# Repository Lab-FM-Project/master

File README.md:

# master
FMProject master folder

Second year FM project. Based on the AR1010 FM chip. We got to play around with it and add any innovations. (Even if its only 10% of the mark!)

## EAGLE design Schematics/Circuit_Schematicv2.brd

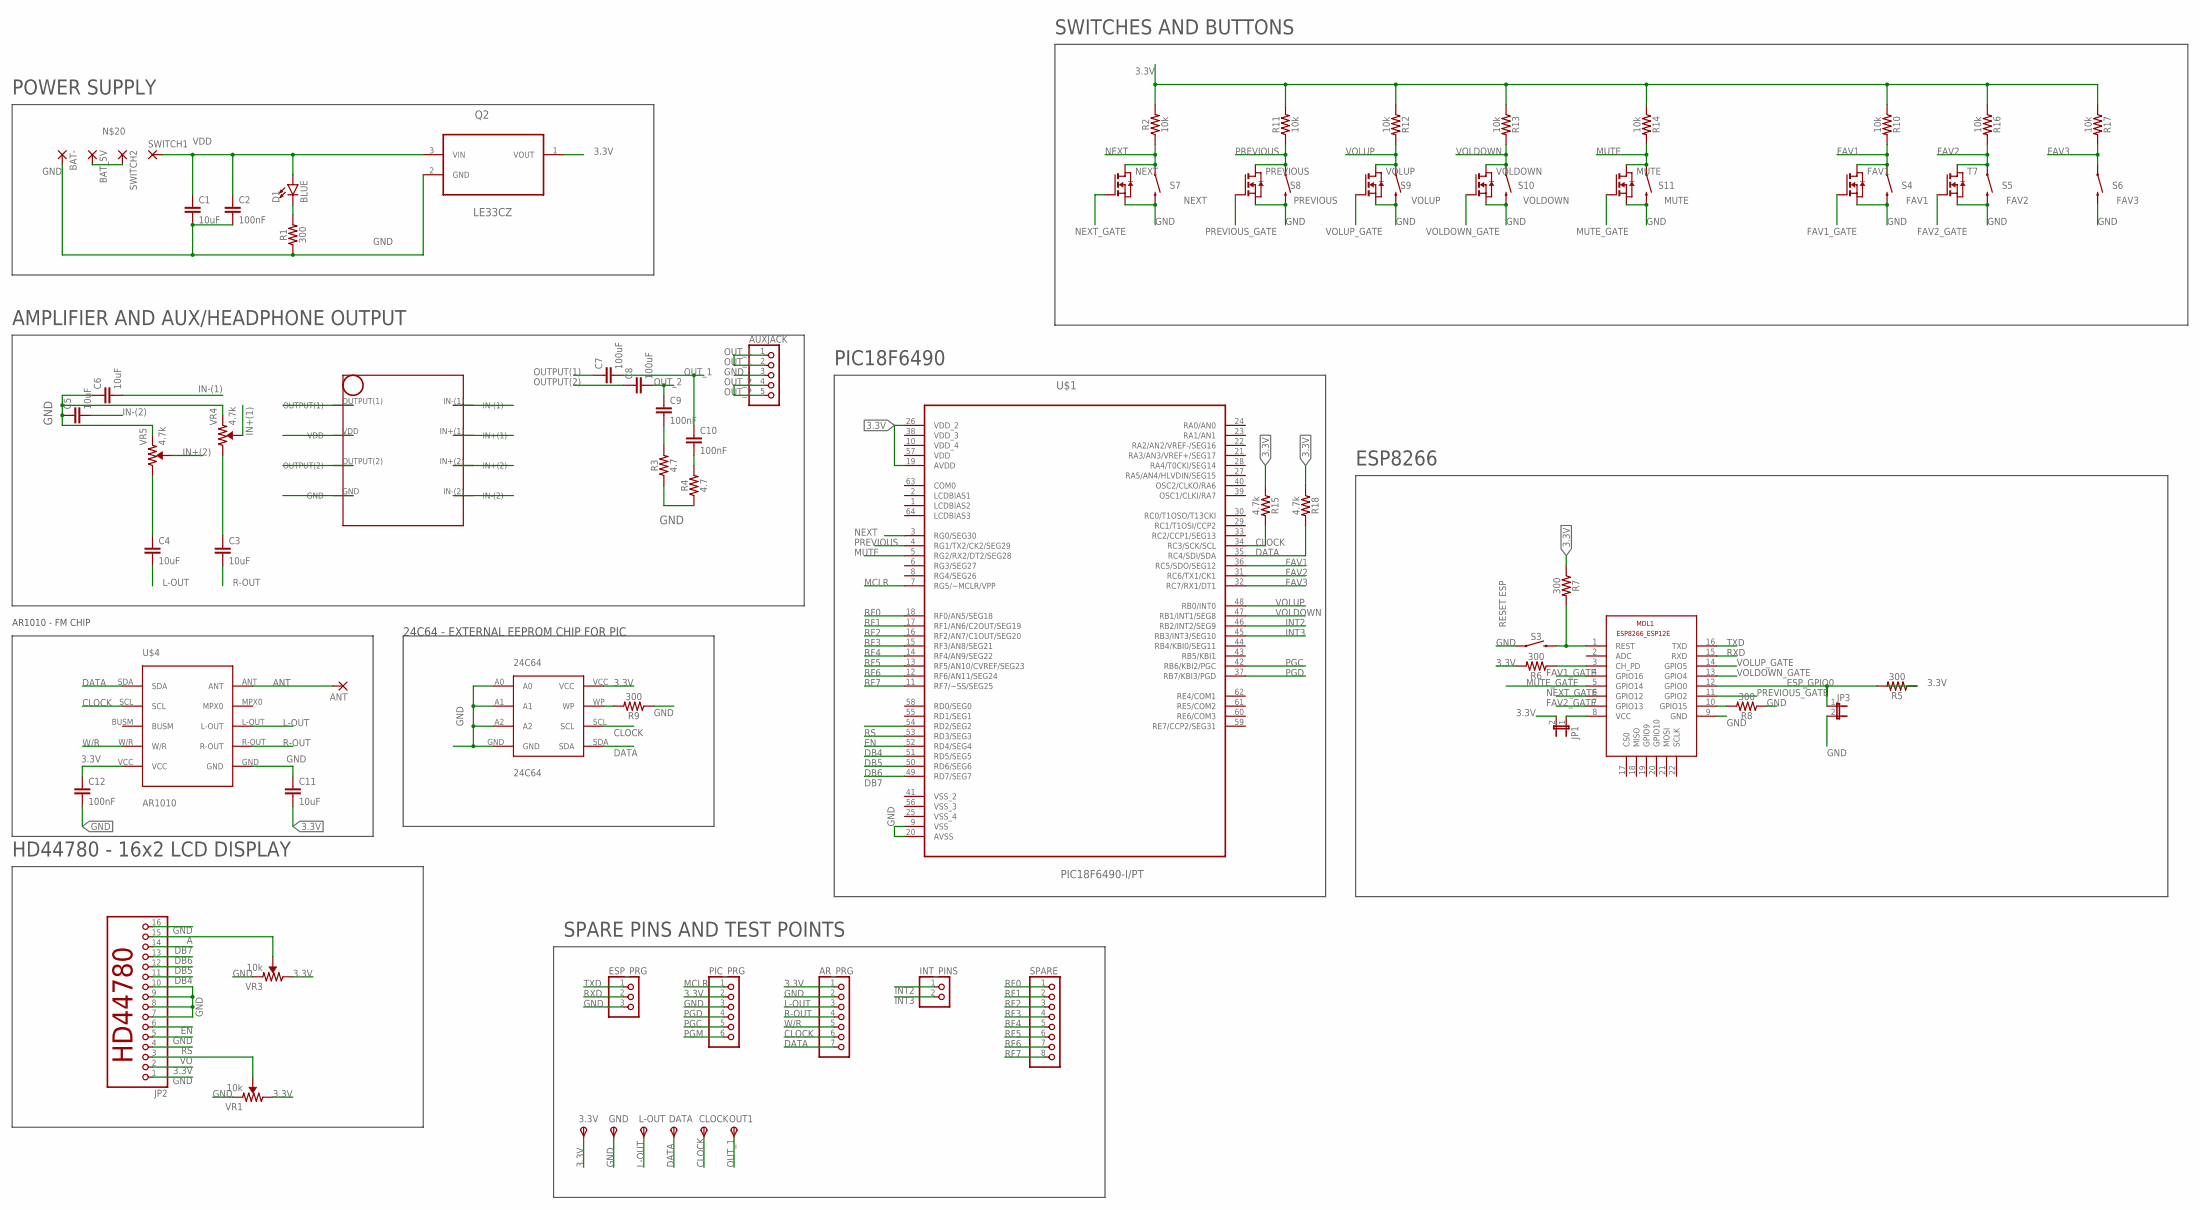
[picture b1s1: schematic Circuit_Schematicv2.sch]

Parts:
3.3V: TPSPAD1-13; P1-13
24C64: 24C64; SOIC-8
ANT: 2,15/1,0
AR_PRG: PINHD-1X7; 1X07
AUXJACK: PINHD-1X5; 1X05
BAT-: 2,15/1,0
BAT_5V: 2,15/1,0
C1, C3, C4, C5, C6, C11: 10uF; 1210
C2, C9, C10, C12: 100nF; 1210
C7, C8: 100uF; 1210
CLOCK: TPSPAD1-13; P1-13
D1: BLUE; LED-1206
DATA: TPSPAD1-13; P1-13
ESP_PRG: PINHD-1X3; 1X03
FAV1: NMOSSOT223; SOT223
GND: TPSPAD1-13; P1-13
INT_PINS: PINHD-1X2; 1X02
JP1, JP3: JP1E; JP1
JP2: LCD16X2HEADER
L-OUT: TPSPAD1-13; P1-13
MDL1: ESP8266-12EESP8266-ESP12E; ESP8266-ESP12E
MUTE: NMOSSOT223; SOT223
NEXT: NMOSSOT223; SOT223
OUT1: TPSPAD1-13; P1-13
PIC_PRG: PINHD-1X6; 1X06
PREVIOUS: NMOSSOT223; SOT223
Q2: LE33CZ; TO127P254X749-3
R1, R5, R6, R7, R8, R9: 300; 0603
R2, R10, R11, R12, R13, R14, R16, R17: 10k; 0603
R3, R4: 4.7; 0603
R15, R18: 4.7k; 0603
S3: RESET ESP; TACTILE_SWITCH_SMD_6.0X3.5MM
S4: FAV1; TACTILE_SWITCH_PTH_6.0MM_KIT
S5: FAV2; TACTILE_SWITCH_PTH_6.0MM_KIT
S6: FAV3; TACTILE_SWITCH_PTH_6.0MM_KIT
S7: NEXT; TACTILE_SWITCH_PTH_6.0MM_KIT
S8: PREVIOUS; TACTILE_SWITCH_PTH_6.0MM_KIT
S9: VOLUP; TACTILE_SWITCH_PTH_6.0MM_KIT
S10: VOLDOWN; TACTILE_SWITCH_PTH_6.0MM_KIT
S11: MUTE; TACTILE_SWITCH_PTH_6.0MM_KIT
SPARE: PINHD-1X8; 1X08
SWITCH1, SWITCH2: 2,15/1,0
T7: NMOSSOT223; SOT223
U$1: PIC18F6490-I/PT; QFP50P1200X1200X120-64N
U$2: TDA2822M
U$4: AR1010
VOLDOWN: NMOSSOT223; SOT223
VOLUP: NMOSSOT223; SOT223
VR1, VR3: 10k; TRIMPOT-SMD-TC33X
VR4, VR5: 4.7k; TRIMPOT-SMD-TC33X

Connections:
3.3V: 3.3V.TP, 24C64.VCC, AR_PRG.1, C11.2, C12.1, JP1.2, JP2.2, PIC_PRG.2, Q2.1 (VOUT), R2.2, R5.1, R6.2, R7.1, R10.1, R11.2, R12.1, R13.1, R14.1, R15.1, R16.1, R17.1, R18.1, U$1.19 (AVDD), U$1.26 (VDD_2), U$4.VCC, VR1.1 (CW), VR3.1 (CW)
A: JP2.15, VR3.2 (WIPER)
ANT: ANT.1, U$4.ANT
CH_PD: MDL1.3 (CH_PD), R6.1
CLOCK: 24C64.SCL, AR_PRG.6, CLOCK.TP, R15.2, U$1.34 (RC3/SCK/SCL), U$4.SCL
DATA: 24C64.SDA, AR_PRG.7, DATA.TP, R18.2, U$1.35 (RC4/SDI/SDA), U$4.SDA
DB4: JP2.11, U$1.52 (RD4/SEG4)
DB5: JP2.12, U$1.51 (RD5/SEG5)
DB6: JP2.13, U$1.50 (RD6/SEG6)
DB7: JP2.14, U$1.49 (RD7/SEG7)
EN: JP2.6, U$1.53 (RD3/SEG3)
ESP_GPIO0: JP3.1, MDL1.12 (GPIO0), R5.2
ESP_VCC: JP1.1, MDL1.8 (VCC)
FAV1: FAV1.2 (D), FAV1.4 (D), R10.2, S4.1, U$1.36 (RC5/SDO/SEG12)
FAV1_GATE: FAV1.1 (G), MDL1.4 (GPIO16)
FAV2: R16.2, S5.1, T7.2 (D), T7.4 (D), U$1.31 (RC6/TX1/CK1)
FAV2_GATE: MDL1.7 (GPIO13), T7.1 (G)
FAV3: R17.2, S6.1, U$1.32 (RC7/RX1/DT1)
GND: 24C64.A0, 24C64.A1, 24C64.A2, 24C64.GND, AR_PRG.2, AUXJACK.3, BAT-.1, C1.2, C2.2, C5.1, C6.1, C11.1, C12.2, ESP_PRG.3, FAV1.3 (S), GND.TP, JP2.1, JP2.5, JP2.7, JP2.8, JP2.9, JP2.10, JP2.16, JP3.2, MDL1.9 (GND), MUTE.3 (S), NEXT.3 (S), PIC_PRG.3, PREVIOUS.3 (S), Q2.2 (GND), R1.1, R3.1, R4.1, R8.1, R9.1, S3.1, S4.3 (2), S5.3 (2), S6.3 (2), S7.3 (2), S8.3 (2), S9.3 (2), S10.3 (2), S11.3 (2), T7.3 (S), U$1.9 (VSS), U$1.20 (AVSS), U$2.GND, U$4.GND, VOLDOWN.3 (S), VOLUP.3 (S), VR1.3 (CCW), VR3.3 (CCW), VR4.3 (CCW), VR5.3 (CCW)
IN+(1): U$2.IN+(1), VR4.2 (WIPER)
IN+(2): U$2.IN+(2), VR5.2 (WIPER)
IN-(1): C6.2, U$2.IN-(1)
IN-(2): C5.2, U$2.IN-(2)
INT2: INT_PINS.1, U$1.46 (RB2/INT2/SEG9)
INT3: INT_PINS.2, U$1.45 (RB3/INT3/SEG10)
L-OUT: AR_PRG.3, C4.2, L-OUT.TP, U$4.L-OUT
MCLR: PIC_PRG.1, U$1.7 (RG5/~MCLR/VPP)
MUTE: MUTE.2 (D), MUTE.4 (D), R14.2, S11.1, U$1.5 (RG2/RX2/DT2/SEG28)
MUTE_GATE: MDL1.5 (GPIO14), MUTE.1 (G)
unnamed: C10.2, R4.2
unnamed: 24C64.WP, R9.2
unnamed: C4.1, VR5.1 (CW)
unnamed: C3.1, VR4.1 (CW)
unnamed: C9.2, R3.2
unnamed: D1.C, R1.2
unnamed: BAT_5V.1, SWITCH2.1
unnamed: MDL1.10 (GPIO15), R8.2
NEXT: NEXT.2 (D), NEXT.4 (D), R2.1, S7.1, U$1.3 (RG0/SEG30)
NEXT_GATE: MDL1.6 (GPIO12), NEXT.1 (G)
OUTPUT(1): C7.1, U$2.OUTPUT(1)
OUTPUT(2): C8.1, U$2.OUTPUT(2)
OUT_1: AUXJACK.1, AUXJACK.2, C7.2, C10.1, OUT1.TP
OUT_2: AUXJACK.4, AUXJACK.5, C8.2, C9.1
PGC: PIC_PRG.5, U$1.42 (RB6/KBI2/PGC)
PGD: PIC_PRG.4, U$1.37 (RB7/KBI3/PGD)
PGM: PIC_PRG.6
PREVIOUS: PREVIOUS.2 (D), PREVIOUS.4 (D), R11.1, S8.1, U$1.4 (RG1/TX2/CK2/SEG29)
PREVIOUS_GATE: MDL1.11 (GPIO2), PREVIOUS.1 (G)
R-OUT: AR_PRG.4, C3.2, U$4.R-OUT
REST: MDL1.1 (REST), R7.2, S3.2
RF0: SPARE.1, U$1.18 (RF0/AN5/SEG18)
RF1: SPARE.2, U$1.17 (RF1/AN6/C2OUT/SEG19)
RF2: SPARE.3, U$1.16 (RF2/AN7/C1OUT/SEG20)
RF3: SPARE.4, U$1.15 (RF3/AN8/SEG21)
RF4: SPARE.5, U$1.14 (RF4/AN9/SEG22)
RF5: SPARE.6, U$1.13 (RF5/AN10/CVREF/SEG23)
RF6: SPARE.7, U$1.12 (RF6/AN11/SEG24)
RF7: SPARE.8, U$1.11 (RF7/~SS/SEG25)
RS: JP2.4, U$1.54 (RD2/SEG2)
RXD: ESP_PRG.2, MDL1.15 (RXD)
TXD: ESP_PRG.1, MDL1.16 (TXD)
VDD: C1.1, C2.1, D1.A, Q2.3 (VIN), SWITCH1.1, U$1.57 (VDD), U$2.VDD
VDD_3: U$1.38 (VDD_3)
VDD_4: U$1.10 (VDD_4)
VO: JP2.3, VR1.2 (WIPER)
VOLDOWN: R13.2, S10.1, U$1.47 (RB1/INT1/SEG8), VOLDOWN.2 (D), VOLDOWN.4 (D)
VOLDOWN_GATE: MDL1.13 (GPIO4), VOLDOWN.1 (G)
VOLUP: R12.2, S9.1, U$1.48 (RB0/INT0), VOLUP.2 (D), VOLUP.4 (D)
VOLUP_GATE: MDL1.14 (GPIO5), VOLUP.1 (G)
VSS_2: U$1.41 (VSS_2)
VSS_3: U$1.56 (VSS_3)
VSS_4: U$1.25 (VSS_4)
W/R: AR_PRG.5, U$4.W/R

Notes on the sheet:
POWER SUPPLY
AMPLIFIER AND AUX/HEADPHONE OUTPUT
SWITCHES AND BUTTONS
AR1010 - FM CHIP
HD44780 - 16x2 LCD DISPLAY
ESP8266
24C64 - EXTERNAL EEPROM CHIP FOR PIC
PIC18F6490
SPARE PINS AND TEST POINTS

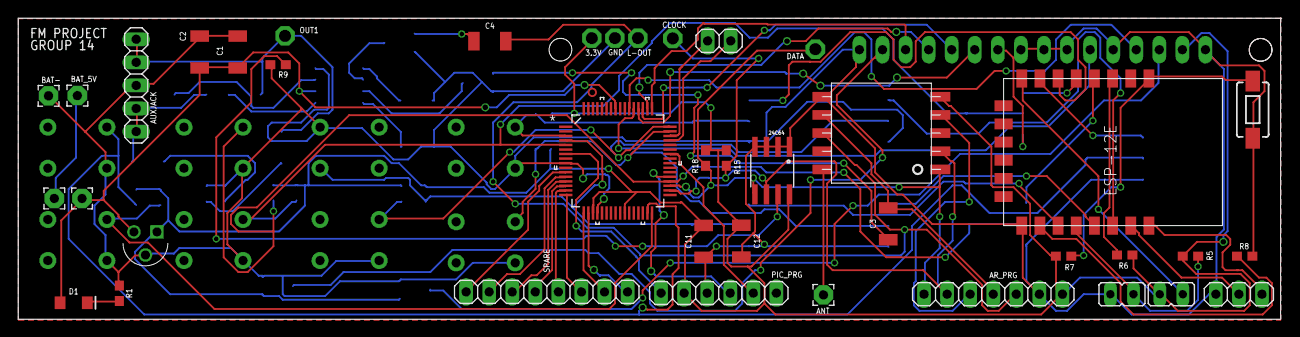
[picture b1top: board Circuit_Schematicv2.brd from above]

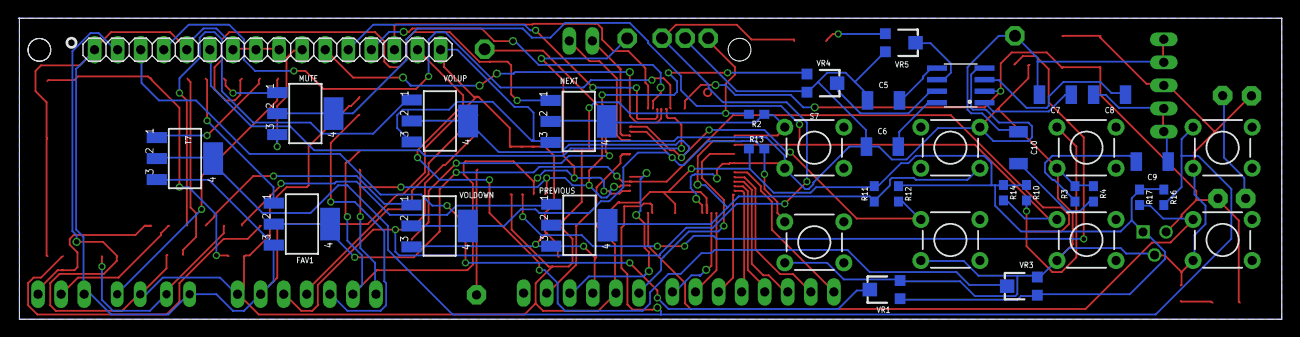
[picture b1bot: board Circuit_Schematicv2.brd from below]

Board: 2 copper layers, 139.1 x 33.1 mm, 77 parts (37 on the bottom side), 67 nets.

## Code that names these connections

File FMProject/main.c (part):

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#pragma config IESO = OFF		// Oscillator Switchover mode disabled 
#pragma config WDT = OFF        // WDT disabled (control through SWDTEN bit)
#pragma config PWRT = ON       // racmod  -> PWRT disabled
#pragma config MCLRE = ON       // MCLR pin enabled; RG5 input pin disabled
#pragma config XINST = OFF      // Instruction set extension disabled
#pragma config BOREN = OFF      // Brown-out controlled by software
#pragma config BORV = 3         // Brown-out voltage set for 2.0V, nominal
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const unsigned int enable[2] = {0, 0}; // Register 11 - Dxxx xxxx xxxx xxxx
extern unsigned int PageSize;
unsigned short CurrentFreq; // stores current frequency
unsigned char hardmute = 0; // stores mute state
unsigned char Home = 0;

unsigned int LastButtonState[6] = {1, 1, 1, 1, 1, 1}; // stores the previous button states
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#define FMASKRDCHAN		0xFF80		// Register 2, channel number bits
#define XS				0			// Exit success
#define XF				1	        // Exit fail
#define PrevChan        PORTGbits.RG0
#define NextChan        PORTGbits.RG1
#define FavChanOne        PORTCbits.RC5
#define FavChanTwo        PORTCbits.RC6
#define FavChanThree      PORTCbits.RC7
#define VolDown           PORTBbits.RB0
#define VolUp         PORTBbits.RB1
#define MUTE         PORTGbits.RG2
#define FMHIGHCHAN		(1080-690)	// Highest FM channel number
#define FMLOWCHAN		(875-690)   // Lowest FM channel number
#define _XTAL_FREQ 8000000
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        if (delaytime >= 65534) {
            delaytime = 0; // reset time variable
            for (int cunt = 0; cunt < 7; cunt++) {
                LastButtonState[cunt] = 1; // reset previous button states
                ButtonState[cunt] = 1; // reset the current button states
            }
        }
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
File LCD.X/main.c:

#define _XTAL_FREQ 8000000


#define RS PORTDbits.RD2
#define EN PORTDbits.RD3
#define D4 PORTDbits.RD4
#define D5 PORTDbits.RD5
#define D6 PORTDbits.RD6
#define D7 PORTDbits.RD7

#include <xc.h>
#include "lcd.h"
#include <stdlib.h>

// BEGIN CONFIG
#pragma config OSC = INTIO7     // Internal osc, RA6=CLKO, RA7=I/O
#pragma config FCMEN = OFF		// Fail-Safe Clock Monitor disabled 
#pragma config IESO = OFF		// Oscillator Switchover mode disabled 
#pragma config WDT = ON        // WDT disabled (control through SWDTEN bit)
#pragma config PWRT = OFF       // racmod  -> PWRT disabled
#pragma config MCLRE = ON       // MCLR pin enabled; RG5 input pin disabled
#pragma config XINST = OFF      // Instruction set extension disabled
#pragma config BOREN = ON      // Brown-out controlled by software
#pragma config BORV = 3         // Brown-out voltage set for 2.0V, nominal
#pragma config STVREN = OFF		// Stack full/underflow will not cause Reset
#pragma config CP = OFF
//END CONFIG

int main()
{
  unsigned int a;
  TRISD = 0x00;
  Lcd_Init();
  
  
  homescreen(89.6);
  while (1)
  { 
    
  }
    
   }

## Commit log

2017-02-16 Buttons
    Added buttons
2017-02-17 Basic Buttons
    Figured that the LCD segments are completely blocking off pretty much
    every single pin that has SEG on it when it is initialised in init() :(
    lost a lot of time
2017-02-17 Uploaded circuit schematics thus far
2017-02-17 Managed to get the buttons working
2017-02-17 Managed to get the FM to work
2017-02-17 Added volume control
2017-02-18 added buttons and cleaned up circuit via net names
2017-02-18 added esp8266-12e and pots for volume adjust on amp
2017-02-19 SEEK is working!
    Only thing to do is to clean up the code and to add incrementations on
    the frequency and volume.
    Also, hopefully set up the EEPROM
2017-02-19 Started working on seek.
    Hard and soft mute is sorted. Need to replace some regImg for FMRead so
    we can read the current data
2017-02-19 seek function seems to work well
2017-02-19 added esp8266 code so far
2017-02-19 Added LCD Project
2017-02-19 moved all files to the fm.h
2017-02-19 Fixed the fm.h
2017-02-19 LCD by David Krolik
2017-02-19 useless changes
2017-02-19 removed lcd
2017-02-19 added lcd
2017-02-19 sorted out lcd for David
2017-02-19 Combined folders
2017-02-20 fixed changes
    github is a bit annoying sometimes.
2017-02-20 recalled the project to a version 2
    Because.
2017-02-20 got mqtt working 2 way between dashboard android app and the esp8266-12e
2017-02-20 updated schematic to include switch and led
2017-02-21 added breakouts for the RAM and DAC ICs for webradio. Need to find or create the correct packages though. Pain in ass.
2017-02-21 changed the fm project
    removed the project and put it locally. Only left the actual files such
    as main.c and the headers to stop git from breaking
2017-02-21 cleaned up the code, separated in new h files
    Unfortunately found out that there is no EEPROM on this PIC so we can’t
    use it to store data :( Having an external one for just three variables
    seems a bit of an overkill.
2017-02-21 added proper eagle parts for ram and custom part for DAC
2017-02-23 Added EEPROM Chip 24C64
2017-02-23 included lcd.h and deleted show_frequency as it was useless for our purpose
2017-02-24 Added ESP controls via NMOS transistors. Lil bit messy.
2017-02-24 extende esp8266 code to do all four buttons. Haven't decided on pins yet.
2017-02-24 Added LCD Folders
2017-02-25 Added AR1010 chip to the schematic, got rid of the breakout for it
2017-02-26 tidied up schematic a bit
2017-02-26 inserted new interrupt functions
2017-02-26 Included code for internet radio. Have started modifying it for our purpose
2017-02-26 Finished Custom Mute Symbol
2017-02-27 cleaned up the schematic
2017-02-27 updated the schematic
2017-02-28 first attempt for 3D print
2017-02-28 wired up esp a bit more
2017-02-28 deleted Alexs lock
2017-02-28 LCD Update
2017-03-01 Added the LCD pinout
2017-03-01 Added EEPROM Chip connections, and finished ESP connections
    We now need to complete it by adding the DAC and RAM chips if we are
    going to use them. Also we should delete the MOSFETs as theyre not
    needed anymore
2017-03-01 added some connectors and cleaned up the code
2017-03-02 added more test pads
2017-03-02 done nothing
2017-03-03 new box design
2017-03-03 started creating PCB
    Gonna be tough
2017-03-06 very close to finishing the PCB design. Very tiny!
2017-03-06 Added dimensions to the pcb. Every little helps.
2017-03-06 recent eagle changes
2017-03-07 Finished the PCB board and schematic
    Changes might have to be made based on the testing on Friday the 10th
    March
2017-03-07 finished off the esp code for all mqtt controls.
2017-03-09 ISSUE WITH STRING COMPARISON IN ESP CODE - WTF?!?!?!?!?
2017-03-09 Solved issue with esp code.
2017-03-10 finished the PCB
2017-03-11 Final changes to make ESP work
2017-03-11 Removed unnecessary switch that I put in on GPIO14
2017-03-13 Updated circuit
2017-03-16 Modified circuit to include transistors
2017-03-18 Final hardware changes and removed serial monitor from esp code in attempt to reduce noise
2017-03-19 Added WifiManager to esp code
2017-03-19 fixing the crapple
2017-03-20 Updated the PS for the PIC
2017-03-20 Added GPIO jumpers instead of switches
2017-03-20 Added a pull up resistor for data clock
    and capacitors for the power lines for AR1010
2017-03-20 fixed the crappy issue
    If error comes up, delete all <<<< HEAD, ====== and all >>>>>
2017-03-20 Fixed David's issue
2017-03-20 Fixed Debounce and Long Press
2017-03-21 Added eprom code to the PIC
2017-03-21 Added new .brd file
2017-03-21 removed some circuit confusions
2017-03-21 Merge remote-tracking branch 'origin/master'
    # Conflicts:
    # .DS_Store
    # Schematics/Circuit_Schematicv2.b#1
    # Schematics/Circuit_Schematicv2.b#2
    # Schematics/Circuit_Schematicv2.b#3
    # Schematics/Circuit_Schematicv2.b#4
2017-03-21 Completed the PCB design
    At the moment it’s 6mils! OOPS. Will try to do it with 10mils.
2017-03-21 github is crazy
2017-03-22 Fixed I think?
    # Conflicts:
    # Schematics/Circuit_Schematicv2.b#1
    # Schematics/Circuit_Schematicv2.b#2
    # Schematics/Circuit_Schematicv2.b#3
    # Schematics/Circuit_Schematicv2.b#4
    # Schematics/Circuit_Schematicv2.b#5
2017-03-22 Finished the PCB design
2017-03-22 Added some code to hopefully tweet somewhere
2017-03-22 Incorporating twitter API on ESP
2017-03-24 Created GERBER Files and BOM
2017-03-29 commit commit commit
2017-04-05 made some pretty pics of circuit
2017-04-16 Finished ESP code. Radio now fully democratised for 2k17.
2017-04-17 Can now set the volume to one up, one down, or 5/10 or 10/10 level from Twitter. Radio to the people!
2017-04-20 First terminal commit
2017-04-20 need David to upload his new code
2017-04-21 Added Array of Buttons
2017-04-24 Added eeprom code that works!
2017-05-05 Added EEPROM Code that actually does work with the frequency ranges we need
2017-05-05 Added saved messages, start up frequency memory and start of code clean up
2017-05-05 Fixed Mute Issue
2017-05-06 More code clean up
2017-05-07 the software is now clean. commented and invincable
    Added station names, fixed screen timer interupt bug, fixed debouce exit
    long press to short press, fixed timer overflow issue, removed fm.h and
    fm_readwite.h
2017-05-09 swapped the channel and volume buttons around
    also added some delays in initialisation.
2017-07-29 removed passwords

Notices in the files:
parts and their libraries:
SparkFun-Capacitors: Licensing: Creative Commons ShareAlike 4.0 International - https://creativecommons.org/licenses/by-sa/4.0
